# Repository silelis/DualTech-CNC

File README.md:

Mach3 and OpenGrbl CNC control unit that drives upto 2.0kW spindle and 40W diode laser.

Complet mechanical and electrtical design.

Required software:
- KiCAD
- QElectroTech
- SolidWorks

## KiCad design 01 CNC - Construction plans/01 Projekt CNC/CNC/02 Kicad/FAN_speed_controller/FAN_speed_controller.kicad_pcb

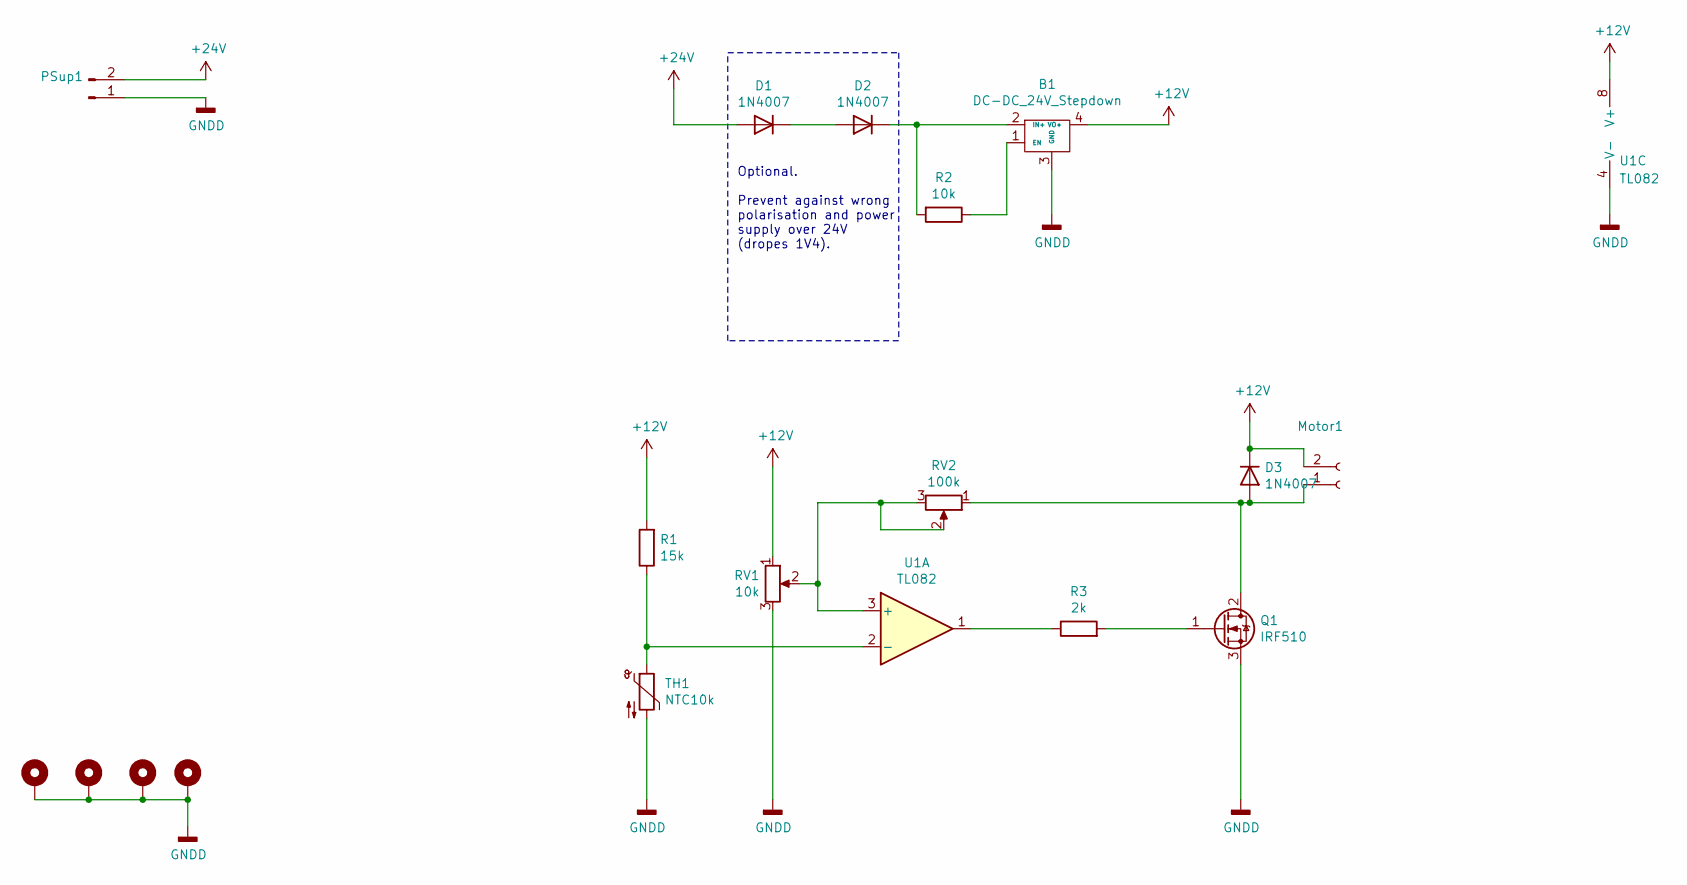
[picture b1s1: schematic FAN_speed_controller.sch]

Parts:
B1: DC-DC_24V_Stepdown; DC-DC_24V_Stepdown_brekout_horizontal
D1, D2, D3: 1N4007; D_DO-41_SOD81_P10.16mm_Horizontal
H1, H2, H3, H4: MountingHole_Pad; MountingHole_3.2mm_M3_DIN965_Pad
Motor1: Conn_01x02_Female; PhoenixContact_MCV_1,5_2-G-3.81_1x02_P3.81mm_Vertical
PSup1: Conn_01x02_Male; PhoenixContact_MCV_1,5_2-G-3.81_1x02_P3.81mm_Vertical
Q1: IRF510; TO-220-3_Horizontal_TabDown
R1: 15k; R_Axial_DIN0207_L6.3mm_D2.5mm_P7.62mm_Horizontal
R2: 10k; R_Axial_DIN0207_L6.3mm_D2.5mm_P7.62mm_Horizontal
R3: 2k; R_Axial_DIN0207_L6.3mm_D2.5mm_P7.62mm_Horizontal
RV1: 10k; Potentiometer_ACP_CA9-H5_Horizontal
RV2: 100k; Potentiometer_ACP_CA9-H5_Horizontal
TH1: NTC10k; R_Axial_DIN0204_L3.6mm_D1.6mm_P2.54mm_Vertical
U1: TL082; DIP-8_W7.62mm_Socket_LongPads

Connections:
+12V: B1.4 (VO+), D3.1 (K), Motor1.2, R1.2, RV1.1, U1.8 (V+)
+24V: D1.2 (A), PSup1.2
GNDD: B1.3 (GND), H1.1, H2.1, H3.1, H4.1, PSup1.1, Q1.3 (S), RV1.3, TH1.2, U1.4 (V-)
unnamed: B1.1 (EN), R2.1
unnamed: B1.2 (IN+), D2.1 (K), R2.2
unnamed: D1.1 (K), D2.2 (A)
unnamed: D3.2 (A), Motor1.1, Q1.2 (D), RV2.1
unnamed: Q1.1 (G), R3.2
unnamed: R1.1, TH1.1, U1.2 (-)
unnamed: R3.1, U1.1
unnamed: RV1.2, RV2.2, RV2.3, U1.3 (+)

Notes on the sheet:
Optional. Prevent against wrong polarisation and power supply over 24V (dropes 1V4).

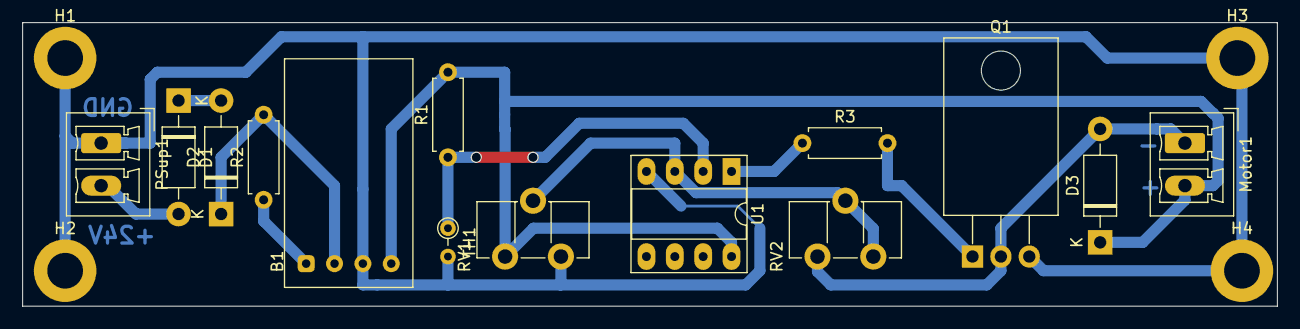
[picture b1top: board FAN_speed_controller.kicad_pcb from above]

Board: 2 copper layers, 112.4 x 25.4 mm, 18 parts (0 on the bottom side), 11 nets.

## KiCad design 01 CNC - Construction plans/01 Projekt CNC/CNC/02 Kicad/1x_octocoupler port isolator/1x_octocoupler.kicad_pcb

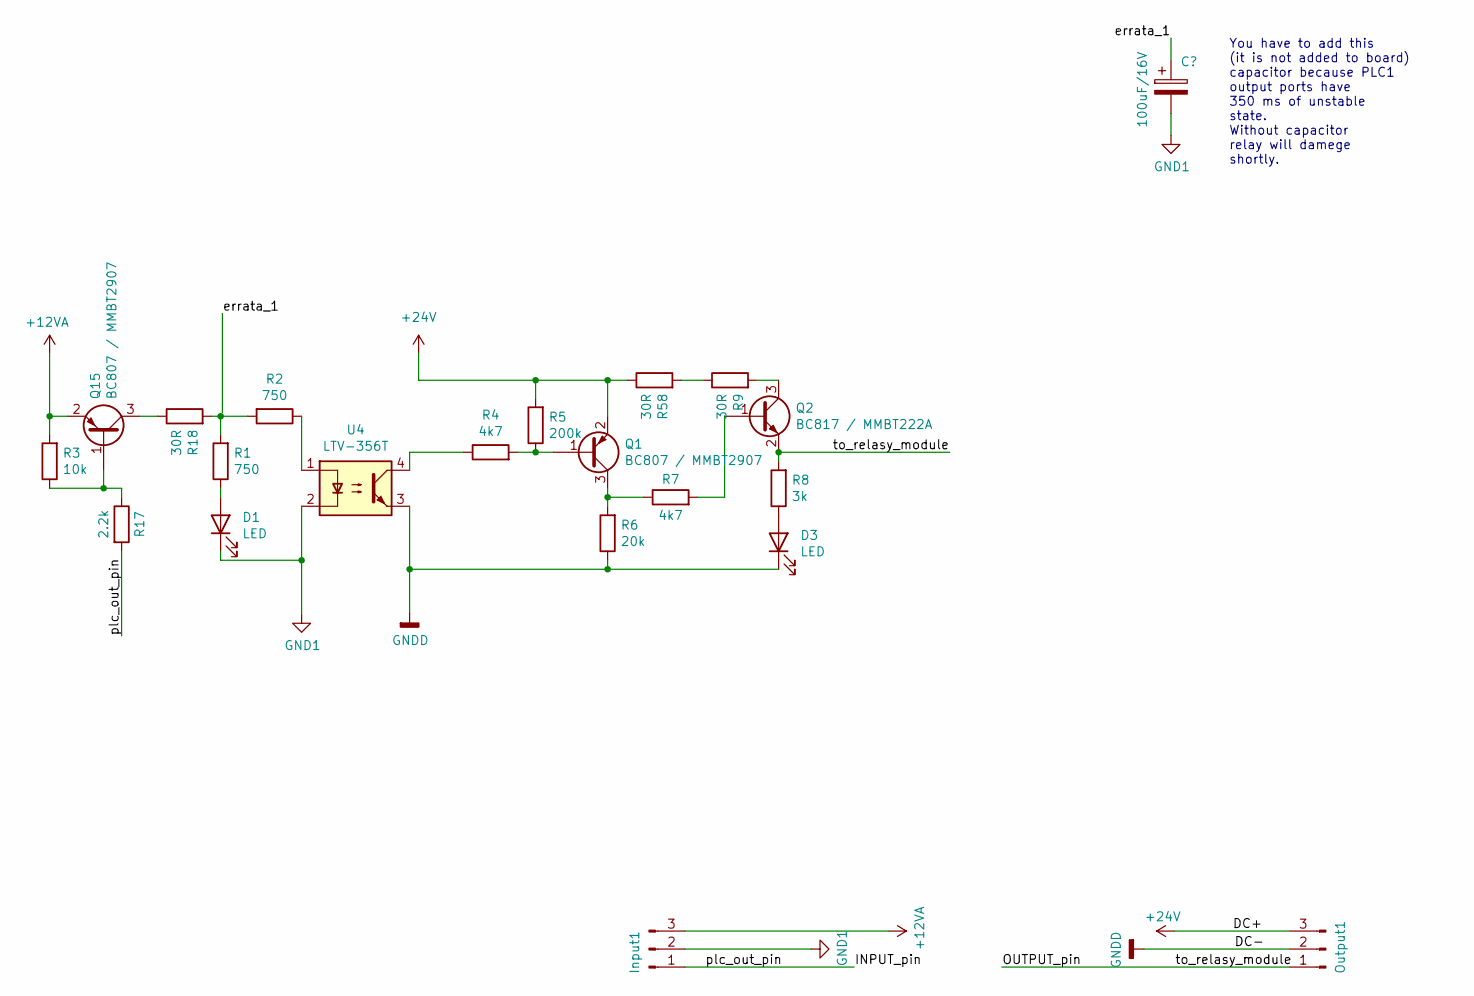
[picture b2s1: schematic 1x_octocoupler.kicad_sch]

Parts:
D1, D3: LED; LED_0603_1608Metric_Pad1.05x0.95mm_HandSolder
Input1: Conn_01x03_Male; PhoenixContact_MCV_1,5_3-G-3.81_1x03_P3.81mm_Vertical
Output1: Conn_01x03_Male; PhoenixContact_MCV_1,5_3-G-3.81_1x03_P3.81mm_Vertical
Q1, Q15: BC807 / MMBT2907; SOT-23
Q2: BC817 / MMBT222A; SOT-23
R1, R2: 750; R_0805_2012Metric
R3: 10k; R_0805_2012Metric
R4, R7: 4k7; R_0805_2012Metric
R5: 200k; R_0805_2012Metric
R6: 20k; R_0805_2012Metric
R8: 3k; R_0805_2012Metric
R9, R18, R58: 30R; R_0805_2012Metric
R17: 2.2k; R_0805_2012Metric
U4: LTV-356T; SO-4_4.4x3.6mm_P2.54mm

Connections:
+12VA: Input1.3, Q15.2 (E), R3.2
+24V: Output1.3, Q1.2 (E), R5.2, R58.1
/INPUT_pin: Input1.1, R17.2
/OUTPUT_pin: Output1.1, Q2.2 (E), R8.2
GND1: D1.1 (K), Input1.2, U4.2
GNDD: D3.1 (K), Output1.2, R6.1, U4.3
unnamed: D1.2 (A), R1.1
unnamed: D3.2 (A), R8.1
unnamed: Q1.1 (B), R4.2, R5.1
unnamed: Q1.3 (C), R6.2, R7.1
unnamed: Q2.1 (B), R7.2
unnamed: Q2.3 (C), R9.2
unnamed: Q15.1 (B), R3.1, R17.1
unnamed: Q15.3 (C), R18.1
unnamed: R1.2, R2.2, R18.2
unnamed: R2.1, U4.1
unnamed: R4.1, U4.4
unnamed: R9.1, R58.2

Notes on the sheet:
You have to add this (it is not added to board) capacitor because PLC1 output ports have 350 ms of unstable state. Without capacitor relay will damege shortly.

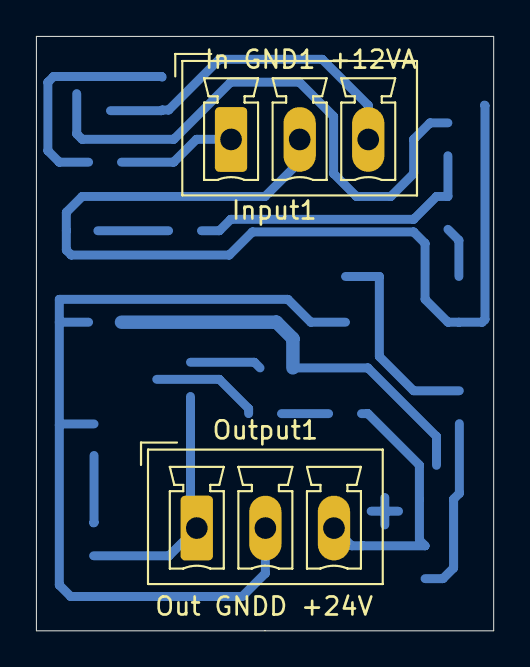
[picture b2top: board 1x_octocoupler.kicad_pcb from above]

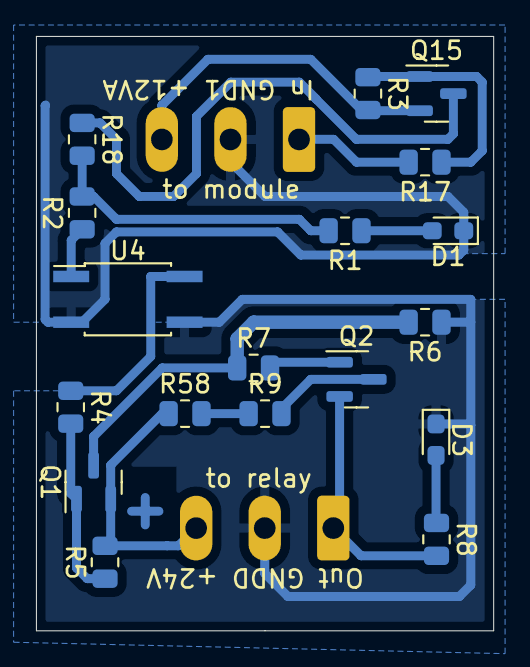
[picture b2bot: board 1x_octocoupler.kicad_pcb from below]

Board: 2 copper layers, 25.4 x 33.0 mm, 20 parts (18 on the bottom side), 18 nets.

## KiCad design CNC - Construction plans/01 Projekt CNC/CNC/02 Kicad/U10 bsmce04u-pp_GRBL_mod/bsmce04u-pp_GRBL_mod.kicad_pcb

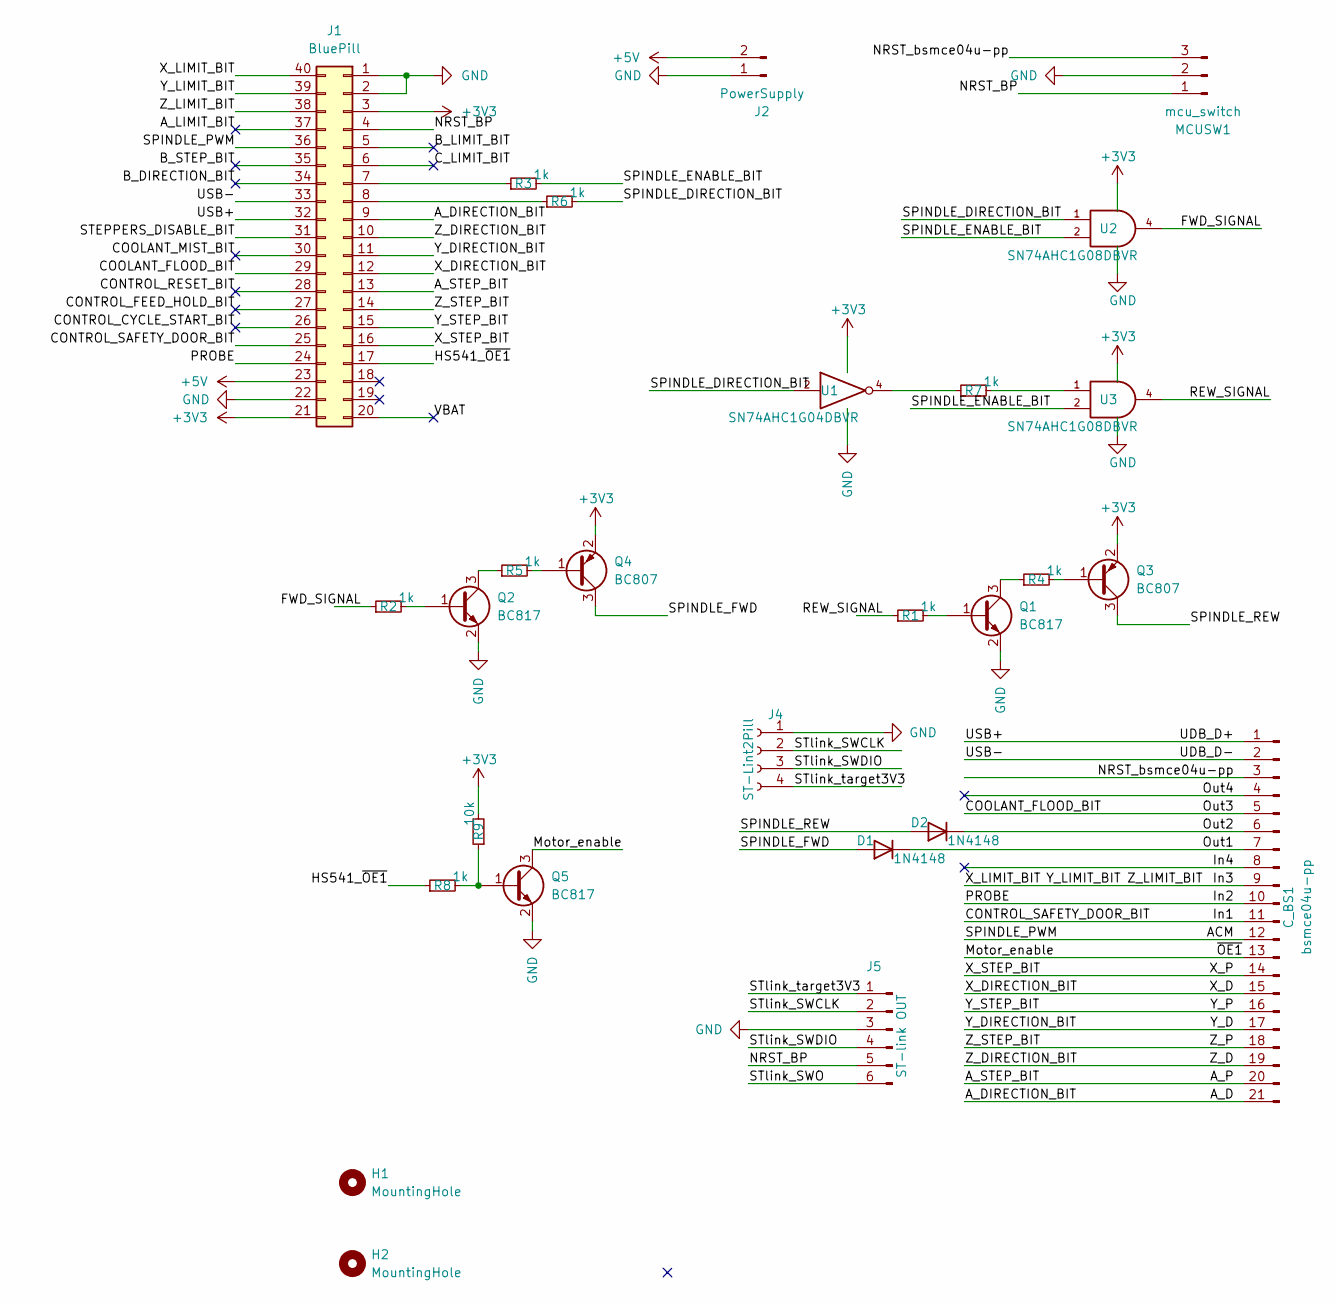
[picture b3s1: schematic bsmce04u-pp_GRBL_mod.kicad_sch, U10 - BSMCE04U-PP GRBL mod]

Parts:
C_BS1: bsmce04u-pp; PinHeader_1x21_P2.54mm_Vertical
D1, D2: 1N4148; D_SOD-123F
H1, H2: MountingHole; MountingHole_3.2mm_M3
J1: BluePill; BluePillPinSocket_2x20_P2.54mm_Vertical
J2: PowerSupply; PinHeader_1x02_P2.54mm_Vertical
J4: ST-Lint2Pill; PinHeader_1x04_P2.54mm_Vertical
J5: ST-link OUT; PinHeader_1x06_P2.54mm_Vertical
MCUSW1: mcu_switch; PinSocket_1x03_P2.54mm_Vertical
Q1, Q2, Q5: BC817; SOT-23
Q3, Q4: BC807; SOT-23
R1, R2, R3, R4, R5, R6, R7, R8: 1k; R_1206_3216Metric
R9: 10k; R_1206_3216Metric
U1: SN74AHC1G04DBVR; SOT-23-5_HandSoldering
U2, U3: SN74AHC1G08DBVR; SOT-23-5_HandSoldering

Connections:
+3V3: J1.3, J1.21, Q3.2 (E), Q4.2 (E), R9.2, U1.5 (VCC), U2.5 (VCC), U3.5 (VCC); also elsewhere on the board
+5V: J1.23, J2.2
/ACM: C_BS1.12, J1.36
/A_D: C_BS1.21, J1.9
/A_LIMIT_BIT: J1.37
/A_P: C_BS1.20, J1.13
/B_DIRECTION_BIT: J1.34
/B_LIMIT_BIT: J1.5
/B_STEP_BIT: J1.35
/CONTROL_CYCLE_START_BIT: J1.26
/CONTROL_FEED_HOLD_BIT: J1.27
/CONTROL_RESET_BIT: J1.28
/CONTROL_SAFETY_DOOR_BIT: C_BS1.11, J1.25
/COOLANT_FLOOD_BIT: C_BS1.5, J1.29
/COOLANT_MIST_BIT: J1.30
/C_LIMIT_BIT: J1.6
/FWD_SIGNAL: R2.1, U2.4
/HS541_~OE1: J1.17, R8.1
/In2: C_BS1.10, J1.24
/In3: C_BS1.9, J1.38, J1.39, J1.40
/In4: C_BS1.8
/Motor_enable: C_BS1.13, Q5.3 (C)
/NRST_BP: J1.4, J5.5, MCUSW1.1
/NRST_bsmce04u-pp: C_BS1.3, MCUSW1.3
/Out1: C_BS1.7, D1.1 (K)
/Out2: C_BS1.6, D2.1 (K)
/Out4: C_BS1.4
/REW_SIGNAL: R1.1, U3.4; also elsewhere on the board
/SPINDLE_DIRECTION_BIT: R6.2, U1.2, U2.1
/SPINDLE_ENABLE_BIT: R3.2, U2.2, U3.2; also elsewhere on the board
/SPINDLE_FWD: D1.2 (A), Q4.3 (C)
/SPINDLE_REW: D2.2 (A), Q3.3 (C)
/STEPPERS_DISABLE_BIT: J1.31
/STlink_SWCLK: J4.2, J5.2
/STlink_SWDIO: J4.3, J5.4
/STlink_SWO: J5.6
/STlink_target3V3: J4.4, J5.1
/UDB_D+: C_BS1.1, J1.32
/UDB_D-: C_BS1.2, J1.33
/VBAT: J1.20
/X_D: C_BS1.15, J1.12
/X_P: C_BS1.14, J1.16
/Y_D: C_BS1.17, J1.11
/Y_P: C_BS1.16, J1.15
/Z_D: C_BS1.19, J1.10
/Z_P: C_BS1.18, J1.14
GND: J1.1, J1.2, J1.22, J2.1, J4.1, J5.3, MCUSW1.2, Q1.2 (E), Q2.2 (E), Q5.2 (E), U1.3 (GND), U2.3 (GND), U3.3 (GND); also elsewhere on the board
unnamed: J1.7, R3.1
unnamed: J1.8, R6.1
unnamed: Q1.1 (B), R1.2
unnamed: Q1.3 (C), R4.1
unnamed: Q2.1 (B), R2.2
unnamed: Q2.3 (C), R5.1
unnamed: Q3.1 (B), R4.2
unnamed: Q4.1 (B), R5.2
unnamed: Q5.1 (B), R8.2, R9.1
unnamed: R7.1, U1.4
unnamed 57: R7.2, U3.1; also elsewhere on the board

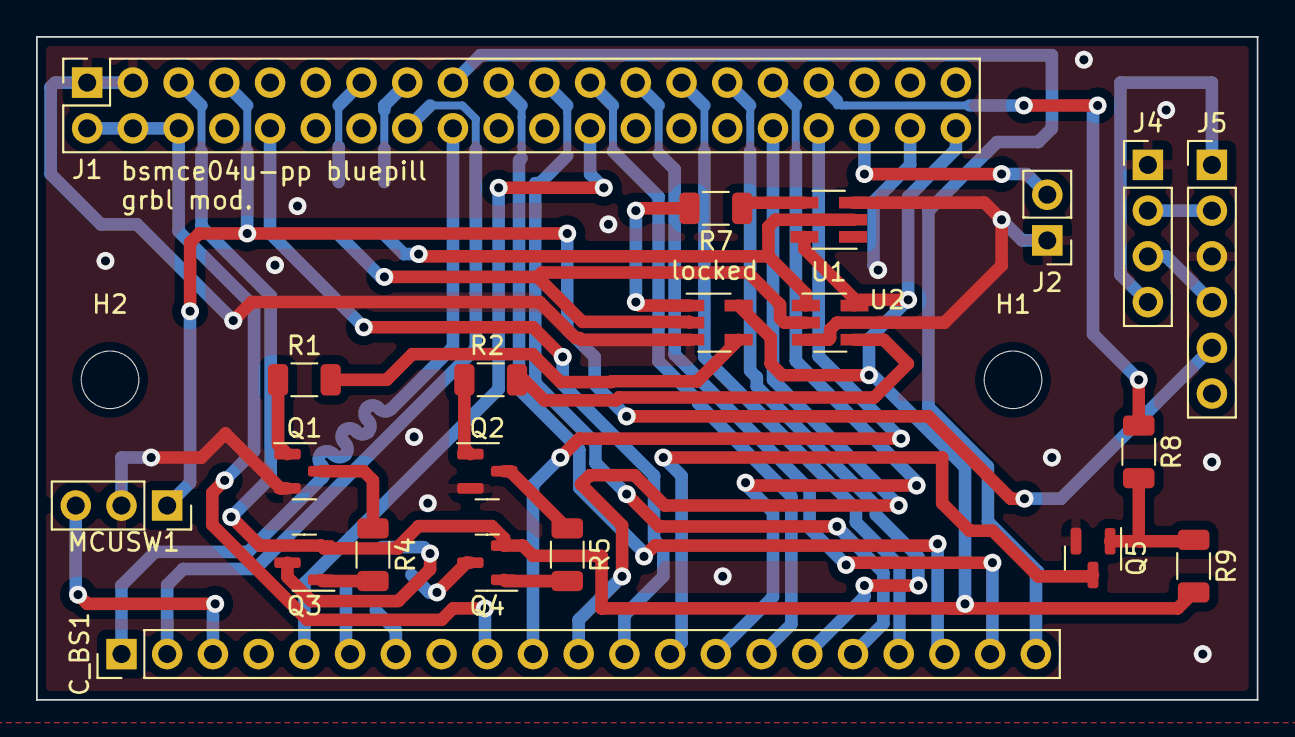
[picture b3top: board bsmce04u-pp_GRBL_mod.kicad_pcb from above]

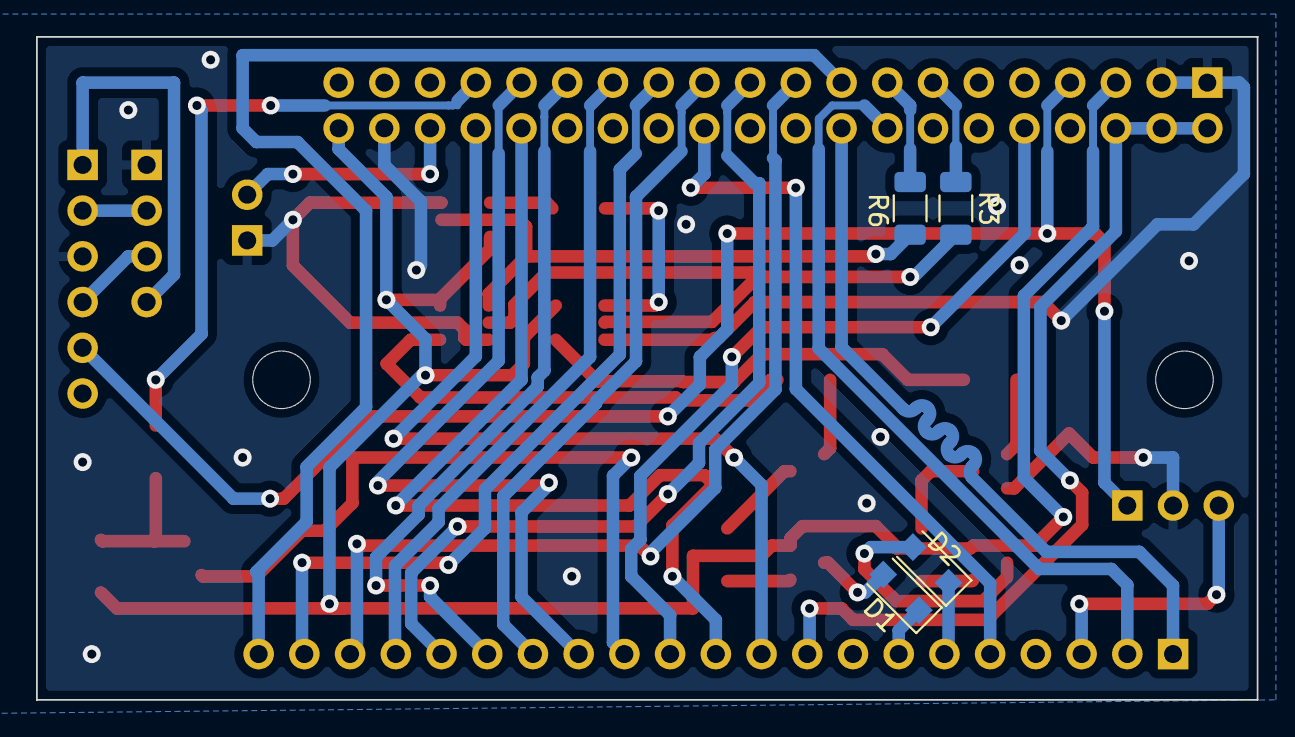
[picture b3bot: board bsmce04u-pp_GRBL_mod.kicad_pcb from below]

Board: 2 copper layers, 67.8 x 36.8 mm, 27 parts (4 on the bottom side), 44 nets.

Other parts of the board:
locked: SN74AHC1G08DBVR; SOT-23-5_HandSoldering

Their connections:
+3V3: locked.5 (VCC); also elsewhere on the board
/REW_SIGNAL: locked.4; also elsewhere on the board
/SPINDLE_ENABLE_BIT: locked.2; also elsewhere on the board
GND: locked.3 (GND); also elsewhere on the board
unnamed 57: locked.1; also elsewhere on the board

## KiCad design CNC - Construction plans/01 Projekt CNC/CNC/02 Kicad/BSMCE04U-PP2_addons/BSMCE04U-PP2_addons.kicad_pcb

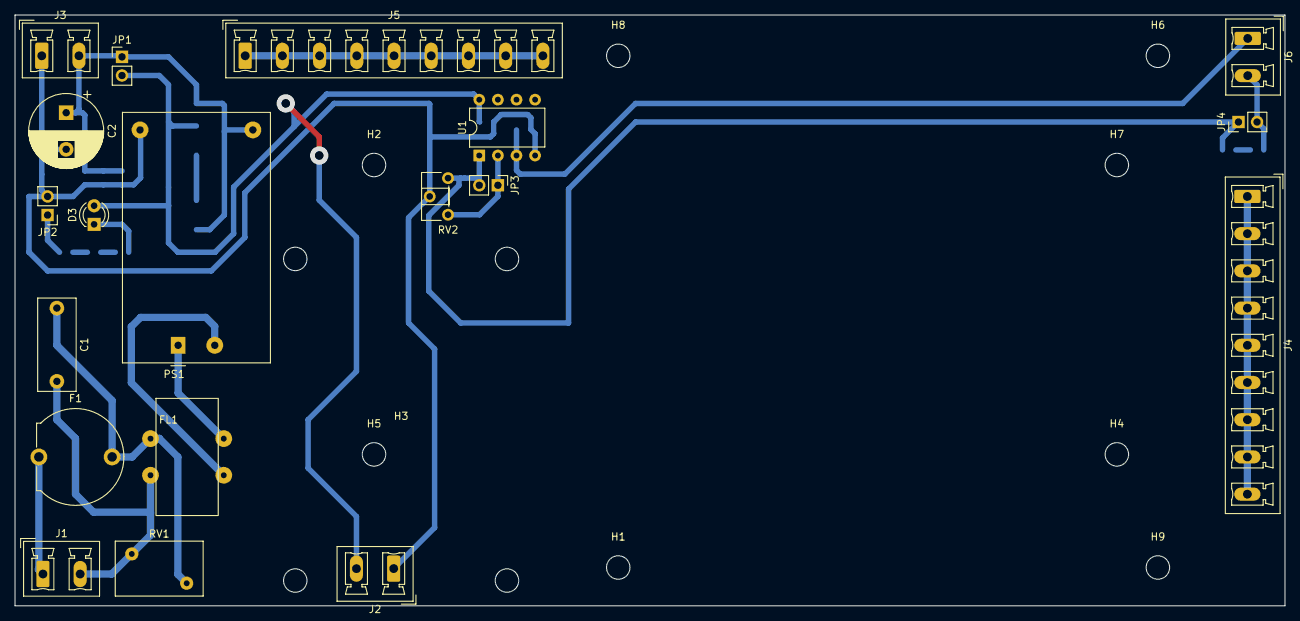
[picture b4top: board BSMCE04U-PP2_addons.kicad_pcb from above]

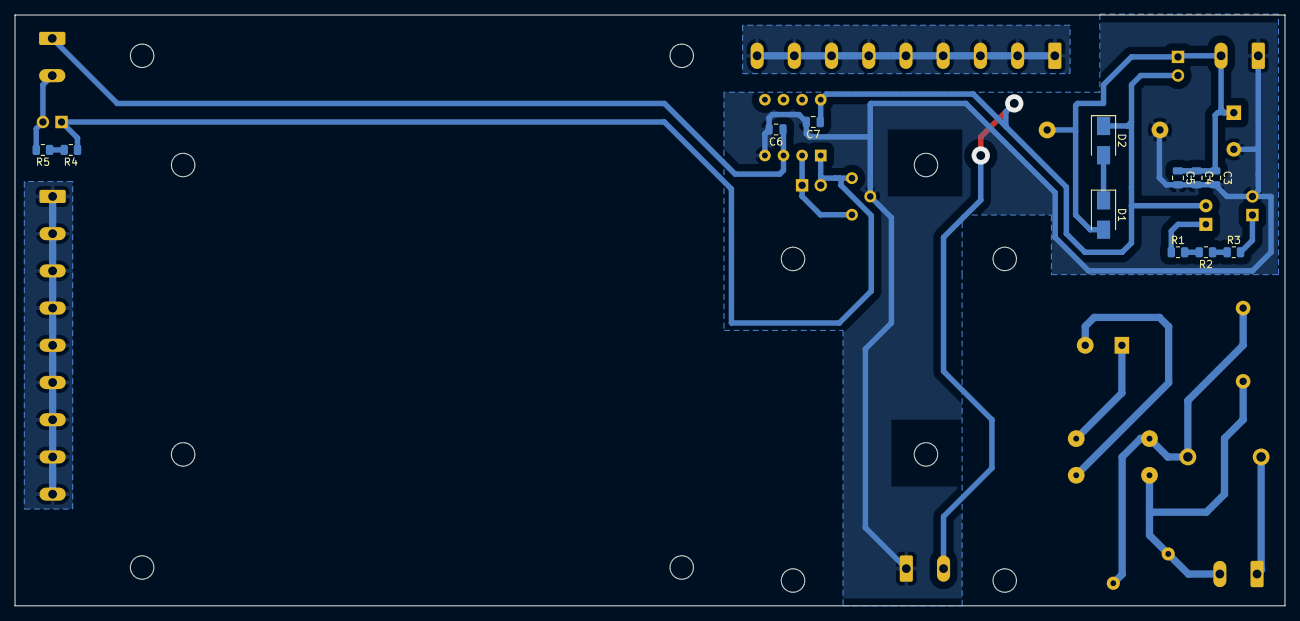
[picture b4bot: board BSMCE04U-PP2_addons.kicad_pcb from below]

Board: 2 copper layers, 173.4 x 80.6 mm, 40 parts (12 on the bottom side), 20 nets.

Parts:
C1: C; C_Disc_D12.5mm_W5.0mm_P10.00mm
C2: C_Polarized; CP_Radial_D10.0mm_P5.00mm
C3, C4, C5: C; C_0805_2012Metric
C6: 1uF; C_0805_2012Metric
C7: 100nF; C_0805_2012Metric
D1, D2: US1K; D_SMA
D3: LED; LED_D3.0mm
F1: ZH24-H; Fuseholder_Cylinder-5x20mm_EATON_H15-V-1_Vertical_Closed
FL1: DTSN-12/10/2.2; DTSN-12_10_2.2
H1, H2, H4, H5, H6, H7, H8, H9: MountingHole; MountingHole_3.2mm_M3
H3: MountingHole; AD584-breakout
J1, J2, J3, J6: Conn_01x02_Male; PhoenixContact_MCV_1,5_2-G-5.08_1x02_P5.08mm_Vertical
J4, J5: Conn_01x09_Female; PhoenixContact_MCV_1,5_9-G-5.08_1x09_P5.08mm_Vertical
JP1, JP2, JP4: Jumper_2_Open; PinHeader_1x02_P2.54mm_Vertical
JP3: Jumper_2_Bridged; PinHeader_1x02_P2.54mm_Vertical
PS1: HLK-PM12; Converter_ACDC_HiLink_HLK-PMxx
R1, R2, R3: 1k; R_0805_2012Metric
R4, R5: 200; R_0805_2012Metric
RV1: Varistor; RV_Disc_D12mm_W7.5mm_P7.5mm
RV2: R_Potentiometer; Potentiometer_ACP_CA6-H2,5_Horizontal
U1: LM358; DIP-8_W7.62mm

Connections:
/(0-10V): J6.2, JP4.2 (B), R5.2
/+12/24VA: C7.1, D2.1 (K), D3.2 (A), J2.2, JP1.2 (B), U1.8 (V+)
/AC_L: F1.1, J1.1
/AC_N: C1.2, FL1.3, J1.2, RV1.2
/PLC_DCM: J5.1, J5.2, J5.3, J5.4, J5.5, J5.6, J5.7, J5.8, J5.9
GNDA: C2.2, C3.2, C4.2, C5.2, C6.2, C7.2, J2.1, J3.1, JP2.2 (B), PS1.3 (-Vout), RV2.2, U1.4 (V-)
GNDD: J4.1, J4.2, J4.3, J4.4, J4.5, J4.6, J4.7, J4.8, J4.9
unnamed: C1.1, F1.2, FL1.1, RV1.1
unnamed: C2.1, C3.1, C4.1, C5.1, D1.2 (A), J3.2, JP1.1 (A), PS1.4 (+Vout)
unnamed: C6.1, J6.1, U1.3 (+)
unnamed: D1.1 (K), D2.2 (A)
unnamed: D3.1 (K), R1.1
unnamed: FL1.2, PS1.1 (AC/L)
unnamed: FL1.4, PS1.2 (AC/N)
unnamed: JP2.1 (A), R3.2
unnamed: JP3.1 (A), RV2.1, U1.2 (-)
unnamed: JP3.2 (B), JP4.1 (A), R4.1, RV2.3, U1.1
unnamed: R1.2, R2.2
unnamed: R2.1, R3.1
unnamed: R4.2, R5.1

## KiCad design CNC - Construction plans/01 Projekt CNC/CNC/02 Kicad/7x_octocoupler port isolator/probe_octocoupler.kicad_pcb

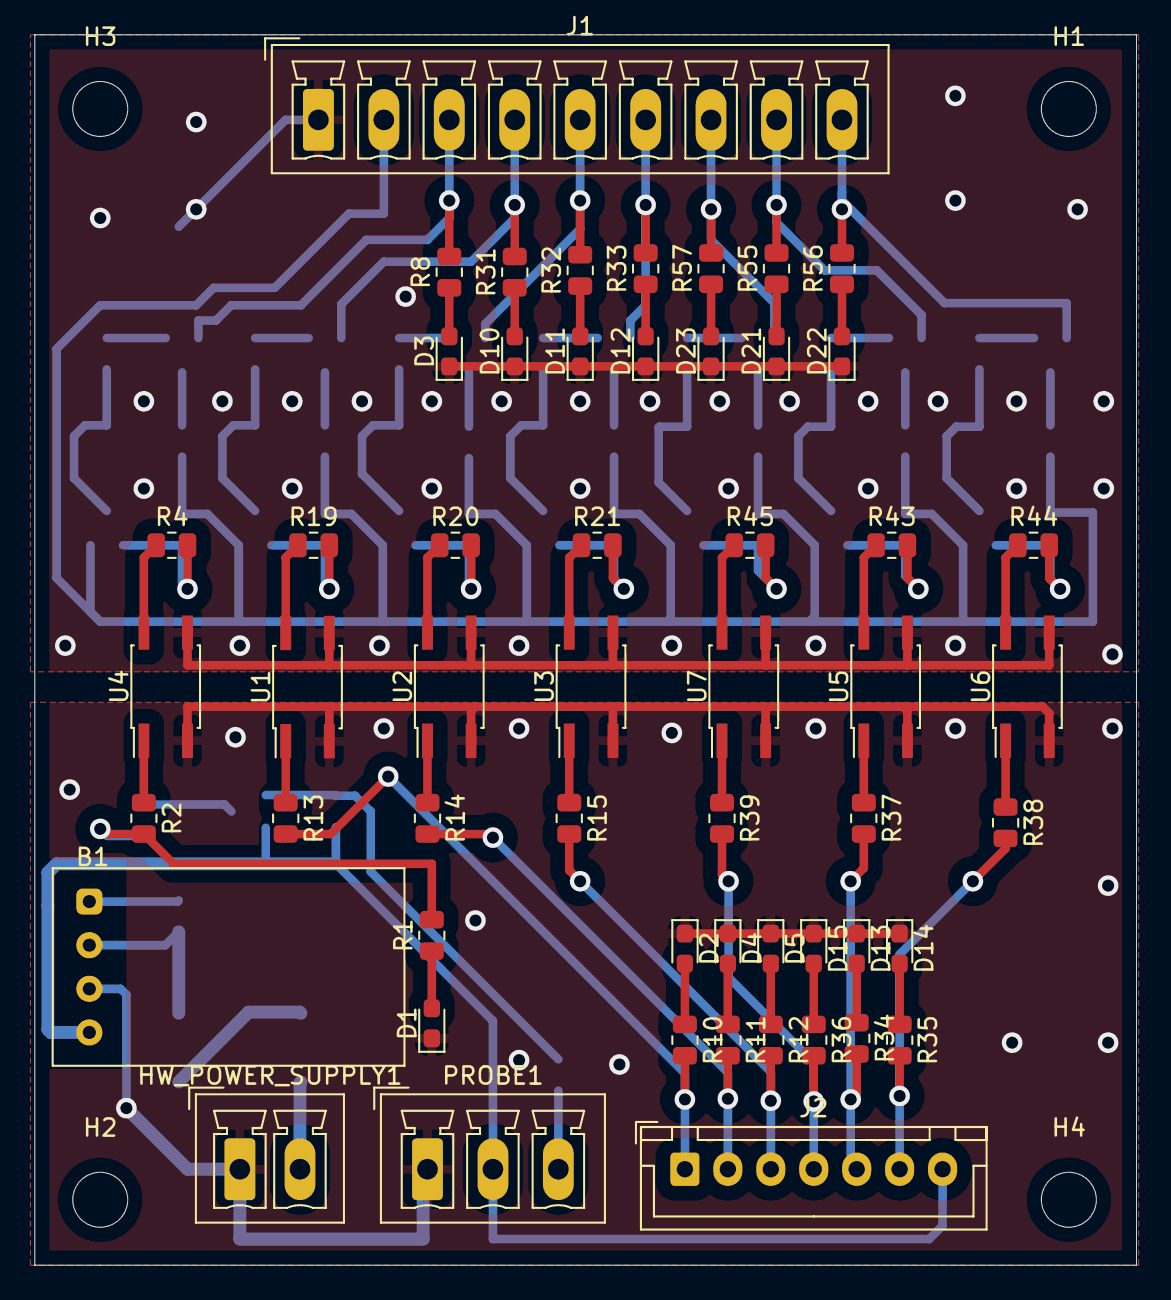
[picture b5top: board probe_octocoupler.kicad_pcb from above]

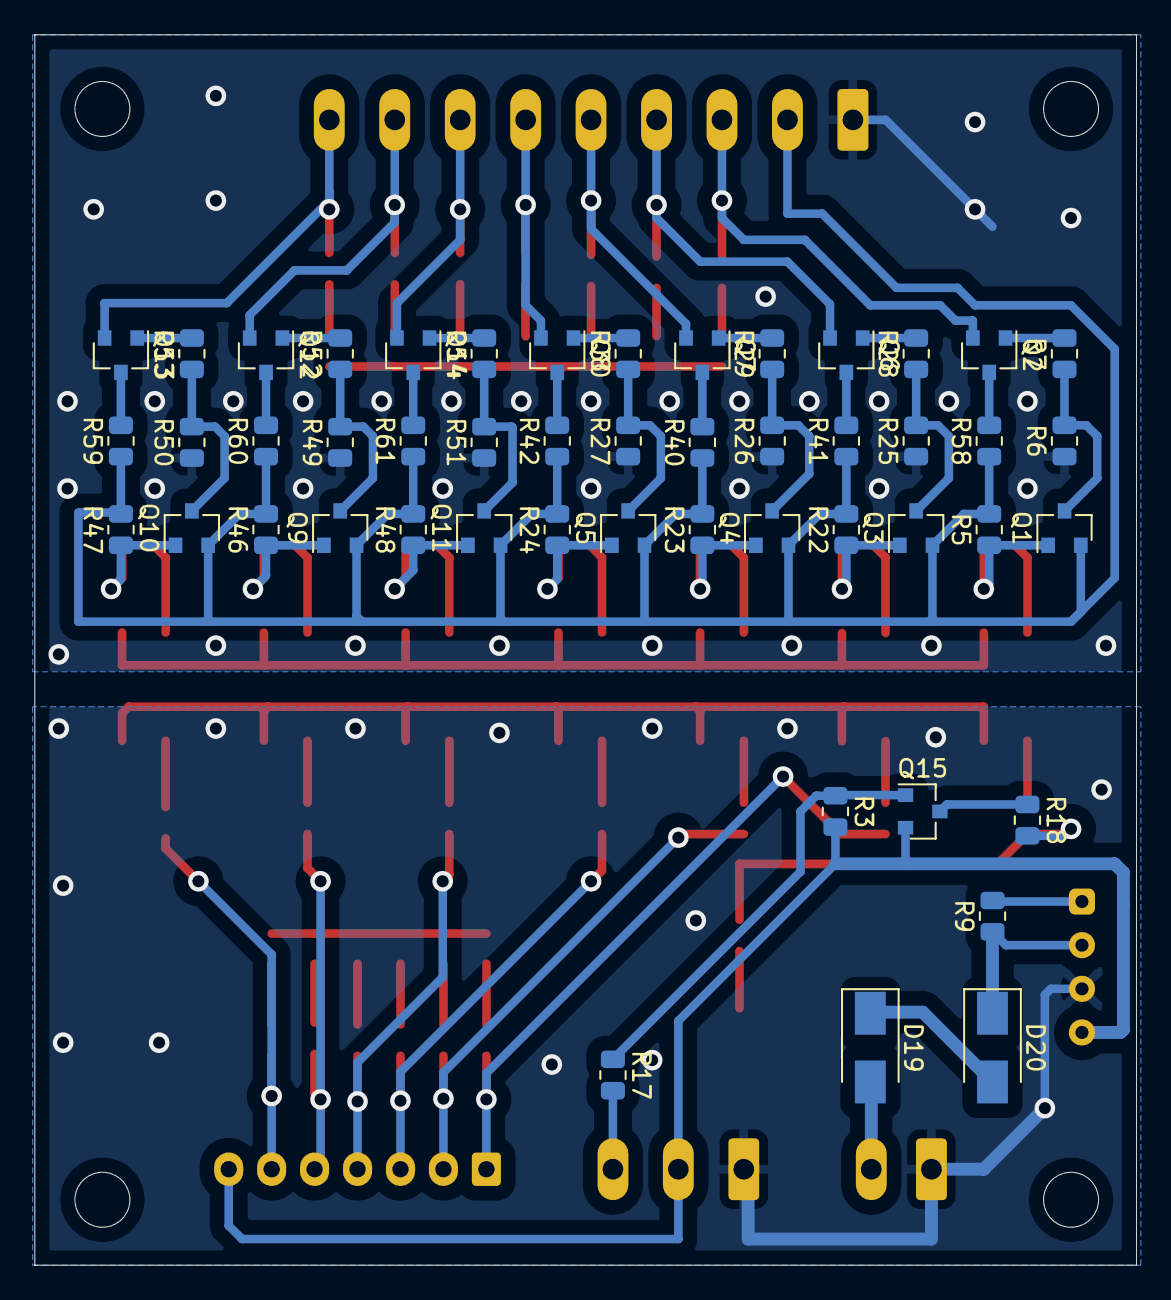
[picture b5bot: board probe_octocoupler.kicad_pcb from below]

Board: 2 copper layers, 64.1 x 71.6 mm, 107 parts (49 on the bottom side), 81 nets.

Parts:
B1: DC-DC_24V_Stepdown; DC-DC_24V_Stepdown_brekout_horizontal
D1, D2, D3, D4, D5, D10, D11, D12, D13, D14, D15, D21, D22, D23: LED; LED_0603_1608Metric_Pad1.05x0.95mm_HandSolder
D19, D20: US1K; D_SMA
H1, H2, H3, H4: MountingHole; MountingHole_3.2mm_M3
HW_POWER_SUPPLY1: Conn_01x02_Male; PhoenixContact_MCV_1,5_2-G-3.5_1x02_P3.50mm_Vertical
J1: Conn_01x09_Male; PhoenixContact_MCV_1,5_9-G-3.81_1x09_P3.81mm_Vertical
J2: XH-6S-10; JST_XH_B7B-XH-A_1x07_P2.50mm_Vertical
PROBE1: Conn_01x03_Male; PhoenixContact_MCV_1,5_3-G-3.81_1x03_P3.81mm_Vertical
Q1, Q3, Q4, Q5, Q9, Q10, Q11, Q15: BC807 / MMBT2907; SOT-23
Q2, Q6, Q7, Q8, Q12, Q13, Q14: BC817 / MMBT222A; SOT-23
R1, R8, R10, R11, R12, R31, R32, R33, R34, R35, R36, R55, R56, R57: 1k5; R_0805_2012Metric
R2, R13, R14, R15, R37, R38, R39: 750; R_0805_2012Metric
R3, R6, R9, R25, R26, R27, R49, R50, R51: 10k; R_0805_2012Metric
R4, R7, R17, R19, R20, R21, R28, R29, R30, R43, R44, R45, R52, R53, R54: 2.2k; R_0805_2012Metric
R5, R22, R23, R24, R46, R47, R48: 100k; R_0805_2012Metric
R18, R40, R41, R42, R58, R59, R60, R61: 30R; R_0805_2012Metric
U1, U2, U3, U4, U5, U6, U7: LTV-356T; SO-4_4.4x3.6mm_P2.54mm

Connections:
+12V: B1.4 (VO+), J2.7, PROBE1.2, Q15.2 (E), R3.2
+12VA: J1.2, Q1.2 (E), Q3.2 (E), Q4.2 (E), Q5.2 (E), Q9.2 (E), Q10.2 (E), Q11.2 (E), R5.2, R22.2, R23.2, R24.2, R40.1, R41.1, R42.1, R46.2, R47.2, R48.2, R58.1, R59.1, R60.1, R61.1
+24V: D19.2 (A), HW_POWER_SUPPLY1.2
/Home_1: J2.1, R10.2, R13.2
/Home_2: J2.2, R11.2, R14.2
/Home_3: J2.3, R12.2, R15.2
/Home_4: J2.4, R36.2, R39.2
/Home_5: J2.5, R34.2, R37.2
/Home_6: J2.6, R35.2, R38.2
/PLC1_input3: J1.4, Q6.2 (E), R31.2
/PLC1_input4: J1.5, Q7.2 (E), R32.2
/PLC1_input5: J1.6, Q8.2 (E), R33.2
/PLC1_input6: J1.7, Q14.2 (E), R57.2
/PLC1_input7: J1.8, Q12.2 (E), R55.2
/PLC1_input8: J1.9, Q13.2 (E), R56.2
/PLC1_input_probe: J1.3, Q2.2 (E), R8.2
GND1: D3.1 (K), D10.1 (K), D11.1 (K), D12.1 (K), D21.1 (K), D22.1 (K), D23.1 (K), J1.1, R6.1, R25.1, R26.1, R27.1, R49.1, R50.1, R51.1, U1.3, U2.3, U3.3, U4.3, U5.3, U6.3, U7.3
GNDD: B1.3 (GND), D1.1 (K), D2.1 (K), D4.1 (K), D5.1 (K), D13.1 (K), D14.1 (K), D15.1 (K), HW_POWER_SUPPLY1.1, PROBE1.1, U1.2, U2.2, U3.2, U4.2, U5.2, U6.2, U7.2
unnamed: B1.1 (EN), R9.2
unnamed: B1.2 (IN+), D20.1 (K), R9.1
unnamed: D1.2 (A), R1.1
unnamed: D2.2 (A), R10.1
unnamed: D3.2 (A), R8.1
unnamed: D4.2 (A), R11.1
unnamed: D5.2 (A), R12.1
unnamed: D10.2 (A), R31.1
unnamed: D11.2 (A), R32.1
unnamed: D12.2 (A), R33.1
unnamed: D13.2 (A), R34.1
unnamed: D14.2 (A), R35.1
unnamed: D15.2 (A), R36.1
unnamed: D19.1 (K), D20.2 (A)
unnamed: D21.2 (A), R55.1
unnamed: D22.2 (A), R56.1
unnamed: D23.2 (A), R57.1
unnamed: PROBE1.3, R17.2
unnamed: Q1.1 (B), R4.2, R5.1
unnamed: Q1.3 (C), R6.2, R7.1
unnamed: Q2.1 (B), R7.2
unnamed: Q2.3 (C), R58.2
unnamed: Q3.1 (B), R19.2, R22.1
unnamed: Q3.3 (C), R25.2, R28.1
unnamed: Q4.1 (B), R20.2, R23.1
unnamed: Q4.3 (C), R26.2, R29.1
unnamed: Q5.1 (B), R21.2, R24.1
unnamed: Q5.3 (C), R27.2, R30.1
unnamed: Q6.1 (B), R28.2
unnamed: Q6.3 (C), R41.2
unnamed: Q7.1 (B), R29.2
unnamed: Q7.3 (C), R40.2
unnamed: Q8.1 (B), R30.2
unnamed: Q8.3 (C), R42.2
unnamed: Q9.1 (B), R43.2, R46.1
unnamed: Q9.3 (C), R49.2, R52.1
unnamed: Q10.1 (B), R44.2, R47.1
unnamed: Q10.3 (C), R50.2, R53.1
unnamed: Q11.1 (B), R45.2, R48.1
unnamed: Q11.3 (C), R51.2, R54.1
unnamed: Q12.1 (B), R52.2
unnamed: Q12.3 (C), R60.2
unnamed: Q13.1 (B), R53.2
unnamed: Q13.3 (C), R59.2
unnamed: Q14.1 (B), R54.2
unnamed: Q14.3 (C), R61.2
unnamed: Q15.1 (B), R3.1, R17.1
unnamed: Q15.3 (C), R18.1
unnamed: R1.2, R2.2, R18.2
unnamed: R2.1, U4.1
unnamed: R4.1, U4.4
unnamed: R13.1, U1.1
unnamed: R14.1, U2.1
unnamed: R15.1, U3.1
unnamed: R19.1, U1.4
unnamed: R20.1, U2.4
unnamed: R21.1, U3.4
unnamed: R37.1, U5.1
unnamed: R38.1, U6.1
unnamed: R39.1, U7.1
unnamed: R43.1, U5.4
unnamed: R44.1, U6.4
unnamed: R45.1, U7.4

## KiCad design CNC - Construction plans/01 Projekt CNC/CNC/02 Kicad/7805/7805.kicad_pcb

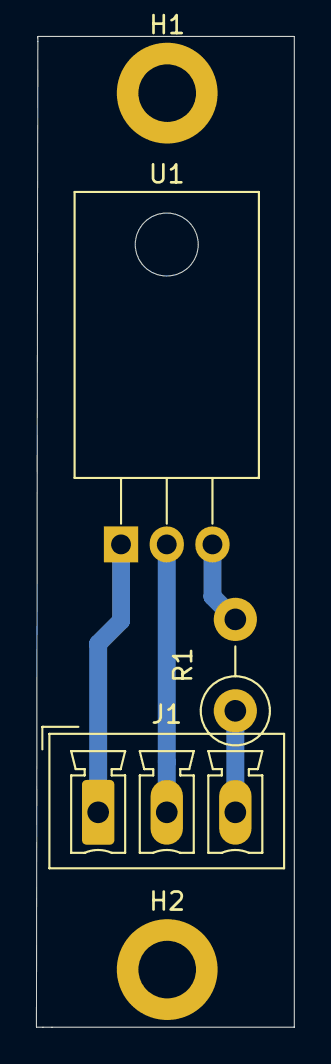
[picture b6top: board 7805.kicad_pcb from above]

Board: 2 copper layers, 14.3 x 55.0 mm, 5 parts (0 on the bottom side), 4 nets.

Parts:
H1, H2: MountingHole_Pad; MountingHole_3.2mm_M3_DIN965_Pad
J1: Conn_01x03_Male; PhoenixContact_MCV_1,5_3-G-3.81_1x03_P3.81mm_Vertical
R1: 10k; R_Axial_DIN0411_L9.9mm_D3.6mm_P5.08mm_Vertical
U1: LM7805_TO220; TO-220-3_Horizontal_TabDown

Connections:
/GND: H1.1, H2.1, J1.2, U1.2
unnamed: J1.1, U1.1
unnamed: J1.3, R1.1
unnamed: R1.2, U1.3

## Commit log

2023-03-24 Pierwszy commit - backup projektu
2023-03-25 Dodano license agrement
2023-03-25 Usunięto plc nvum i jego dokumentację
2023-03-26 Dodano pliki Kickstarter
2023-03-27 Adjustments
2023-03-29 Electrical file updates
2024-04-15 Mach3 profiles update
2024-04-16 poprawiono ustawienia GBRL sterownika
2024-05-03 aktualizacja prędkości w konfigach
2025-01-11 make project public
2025-01-11 README.md
